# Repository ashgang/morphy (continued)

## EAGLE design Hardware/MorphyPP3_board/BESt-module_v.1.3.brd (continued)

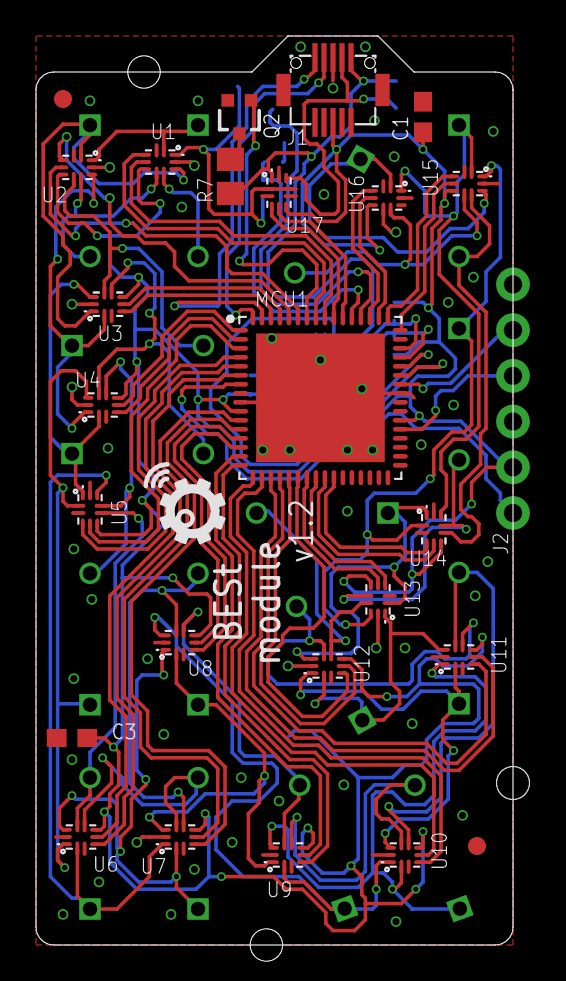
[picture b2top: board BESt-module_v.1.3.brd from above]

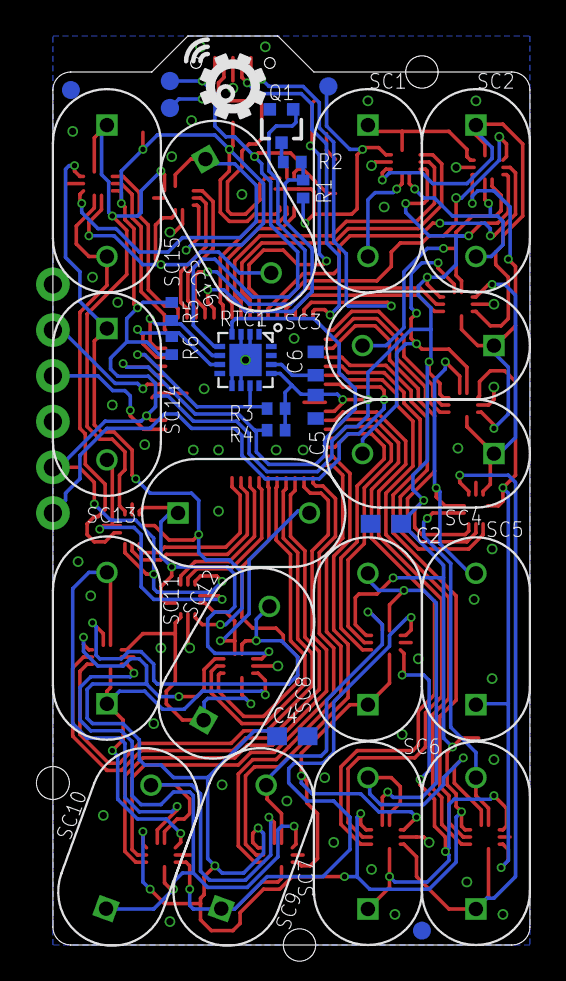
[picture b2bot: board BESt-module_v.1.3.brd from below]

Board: 2 copper layers, 26.5 x 50.5 mm, 61 parts (34 on the bottom side), 86 nets.

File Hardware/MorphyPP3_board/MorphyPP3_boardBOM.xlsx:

Comment | Description | Designator | Footprint | LibRef | Quantity
0.1uF | 0.1碌F ceramic capacitors A capacitor is a passive two-terminal electrical compo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 | C1, C2, C3, C4 | 0603 | 0.1UF-0603-25V-5% | 4
C-USC0402 | CAPACITOR, American symbol | C5, C6 | C0402 | C-USC0402 | 2
FIDUCIAL1X2 | Fiducial Alignment Points Point-of-reference for pick-and-place machines and ot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 | FD1, FD2, FD3, FD4 | FIDUCIAL-1X2 | FIDUCIAL1X2 | 4
AMPHENOL-BERGSTAK®-10POSPLUG | Amphenol鈥檚 BergStak庐 0.5mm is a comprehensive and versatile board-to-board solu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 | J1 | 10132797-10POS-PLUG | AMPHENOL-BERGSTAK®-10POSPLUG | 1
CONN_06NO_SILK_NO_POP | Multi connection point. Often used as Generic Header-pin footprint for 0.1 inch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 | J2 | 1X06_NO_SILK | CONN_06NO_SILK_NO_POP | 1
IIOT |  | LOGO1, LOGO2 | IIOT | IIOT | 2
PIC18(L)F65/66K40MR | 64-Pin, Low-Power, High-Performance Microcontrollers with XLP Technology | MCU1 | QFN50P900X900X100-65T715N | PIC18(L)F65/66K40MR | 1
310mA/60V/1.6Ω | N-channel MOSFETs Voltage controlled devices that allow control of high current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 | Q1, Q2 | SOT323 | MOSFET-NCH-2N7002PW | 2
R-EU_R0402 | RESISTOR, European symbol | R1, R2, R3, R4, R5, R6 | R0402 | R-EU_R0402 | 6
R-US_R0805 | RESISTOR, American symbol | R7 | R0805 | R-US_R0805 | 1
AB1805 |  | RTC1 | QFN-16-3X3 | AB1805 | 1
PM-5R0H/V104-R-VER | CAP 100MF -20% +80% 5V T/H | SC1, SC2, SC3, SC4, SC5, SC6, SC7, SC8, SC9, SC10, SC11, SC12, SC13, SC14, SC15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 | EATON-13X11.3X6-V | PM-5R0H/V104-R-VER | 16
TEST-POINT3X4 | SparkFun Test Points Bare copper test points for troubleshooting or In-Circuit-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 | TP1, TP2, TP3 | PAD.03X.04 | TEST-POINT3X4 | 3
ADG824 | 0.5 鈩?CMOS 1.65 V to 3.6 V Dual SPDT/2:1 Mux in Mini LFCSP Package | U1, U2, U3, U4, U5, U6, U7, U8, U9, U10, U11, U12, U13, U14, U15, U16, U17 | CP-10-10 | ADG824 | 17

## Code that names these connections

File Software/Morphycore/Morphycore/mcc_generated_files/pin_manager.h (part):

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// get/set C13_N_SW aliases
#define C13_N_SW_TRIS                 TRISAbits.TRISA1
#define C13_N_SW_LAT                  LATAbits.LATA1
#define C13_N_SW_PORT                 PORTAbits.RA1
#define C13_N_SW_WPU                  WPUAbits.WPUA1
#define C13_N_SW_OD                   ODCONAbits.ODCA1
#define C13_N_SW_ANS                  ANSELAbits.ANSELA1
#define C13_N_SW_SetHigh()            do { LATAbits.LATA1 = 1; } while(0)
#define C13_N_SW_SetLow()             do { LATAbits.LATA1 = 0; } while(0)
#define C13_N_SW_Toggle()             do { LATAbits.LATA1 = ~LATAbits.LATA1; } while(0)
#define C13_N_SW_GetValue()           PORTAbits.RA1
#define C13_N_SW_SetDigitalInput()    do { TRISAbits.TRISA1 = 1; } while(0)
#define C13_N_SW_SetDigitalOutput()   do { TRISAbits.TRISA1 = 0; } while(0)
#define C13_N_SW_SetPullup()          do { WPUAbits.WPUA1 = 1; } while(0)
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// get/set C12_N_SW aliases
#define C12_N_SW_TRIS                 TRISAbits.TRISA3
#define C12_N_SW_LAT                  LATAbits.LATA3
#define C12_N_SW_PORT                 PORTAbits.RA3
#define C12_N_SW_WPU                  WPUAbits.WPUA3
#define C12_N_SW_OD                   ODCONAbits.ODCA3
#define C12_N_SW_ANS                  ANSELAbits.ANSELA3
#define C12_N_SW_SetHigh()            do { LATAbits.LATA3 = 1; } while(0)
#define C12_N_SW_SetLow()             do { LATAbits.LATA3 = 0; } while(0)
#define C12_N_SW_Toggle()             do { LATAbits.LATA3 = ~LATAbits.LATA3; } while(0)
#define C12_N_SW_GetValue()           PORTAbits.RA3
#define C12_N_SW_SetDigitalInput()    do { TRISAbits.TRISA3 = 1; } while(0)
#define C12_N_SW_SetDigitalOutput()   do { TRISAbits.TRISA3 = 0; } while(0)
#define C12_N_SW_SetPullup()          do { WPUAbits.WPUA3 = 1; } while(0)
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// get/set C15_N_SW aliases
#define C15_N_SW_TRIS                 TRISBbits.TRISB0
#define C15_N_SW_LAT                  LATBbits.LATB0
#define C15_N_SW_PORT                 PORTBbits.RB0
#define C15_N_SW_WPU                  WPUBbits.WPUB0
#define C15_N_SW_OD                   ODCONBbits.ODCB0
#define C15_N_SW_ANS                  ANSELBbits.ANSELB0
#define C15_N_SW_SetHigh()            do { LATBbits.LATB0 = 1; } while(0)
#define C15_N_SW_SetLow()             do { LATBbits.LATB0 = 0; } while(0)
#define C15_N_SW_Toggle()             do { LATBbits.LATB0 = ~LATBbits.LATB0; } while(0)
#define C15_N_SW_GetValue()           PORTBbits.RB0
#define C15_N_SW_SetDigitalInput()    do { TRISBbits.TRISB0 = 1; } while(0)
#define C15_N_SW_SetDigitalOutput()   do { TRISBbits.TRISB0 = 0; } while(0)
#define C15_N_SW_SetPullup()          do { WPUBbits.WPUB0 = 1; } while(0)
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// get/set LowVoltagePin aliases
#define LowVoltagePin_TRIS                 TRISBbits.TRISB7
#define LowVoltagePin_LAT                  LATBbits.LATB7
#define LowVoltagePin_PORT                 PORTBbits.RB7
#define LowVoltagePin_WPU                  WPUBbits.WPUB7
#define LowVoltagePin_OD                   ODCONBbits.ODCB7
#define LowVoltagePin_ANS                  ANSELBbits.ANSELB7
#define LowVoltagePin_SetHigh()            do { LATBbits.LATB7 = 1; } while(0)
#define LowVoltagePin_SetLow()             do { LATBbits.LATB7 = 0; } while(0)
#define LowVoltagePin_Toggle()             do { LATBbits.LATB7 = ~LATBbits.LATB7; } while(0)
#define LowVoltagePin_GetValue()           PORTBbits.RB7
#define LowVoltagePin_SetDigitalInput()    do { TRISBbits.TRISB7 = 1; } while(0)
#define LowVoltagePin_SetDigitalOutput()   do { TRISBbits.TRISB7 = 0; } while(0)
#define LowVoltagePin_SetPullup()          do { WPUBbits.WPUB7 = 1; } while(0)
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// get/set VSYS_SW aliases
#define VSYS_SW_TRIS                 TRISDbits.TRISD1
#define VSYS_SW_LAT                  LATDbits.LATD1
#define VSYS_SW_PORT                 PORTDbits.RD1
#define VSYS_SW_WPU                  WPUDbits.WPUD1
#define VSYS_SW_OD                   ODCONDbits.ODCD1
#define VSYS_SW_ANS                  ANSELDbits.ANSELD1
#define VSYS_SW_SetHigh()            do { LATDbits.LATD1 = 1; } while(0)
#define VSYS_SW_SetLow()             do { LATDbits.LATD1 = 0; } while(0)
#define VSYS_SW_Toggle()             do { LATDbits.LATD1 = ~LATDbits.LATD1; } while(0)
#define VSYS_SW_GetValue()           PORTDbits.RD1
#define VSYS_SW_SetDigitalInput()    do { TRISDbits.TRISD1 = 1; } while(0)
#define VSYS_SW_SetDigitalOutput()   do { TRISDbits.TRISD1 = 0; } while(0)
#define VSYS_SW_SetPullup()          do { WPUDbits.WPUD1 = 1; } while(0)
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// get/set VEH_SW aliases
#define VEH_SW_TRIS                 TRISDbits.TRISD2
#define VEH_SW_LAT                  LATDbits.LATD2
#define VEH_SW_PORT                 PORTDbits.RD2
#define VEH_SW_WPU                  WPUDbits.WPUD2
#define VEH_SW_OD                   ODCONDbits.ODCD2
#define VEH_SW_ANS                  ANSELDbits.ANSELD2
#define VEH_SW_SetHigh()            do { LATDbits.LATD2 = 1; } while(0)
#define VEH_SW_SetLow()             do { LATDbits.LATD2 = 0; } while(0)
#define VEH_SW_Toggle()             do { LATDbits.LATD2 = ~LATDbits.LATD2; } while(0)
#define VEH_SW_GetValue()           PORTDbits.RD2
#define VEH_SW_SetDigitalInput()    do { TRISDbits.TRISD2 = 1; } while(0)
#define VEH_SW_SetDigitalOutput()   do { TRISDbits.TRISD2 = 0; } while(0)
#define VEH_SW_SetPullup()          do { WPUDbits.WPUD2 = 1; } while(0)
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// get/set channel_AND3 aliases
#define channel_AND3_TRIS                 TRISDbits.TRISD3
#define channel_AND3_LAT                  LATDbits.LATD3
#define channel_AND3_PORT                 PORTDbits.RD3
#define channel_AND3_WPU                  WPUDbits.WPUD3
#define channel_AND3_OD                   ODCONDbits.ODCD3
#define channel_AND3_ANS                  ANSELDbits.ANSELD3
#define channel_AND3_SetHigh()            do { LATDbits.LATD3 = 1; } while(0)
#define channel_AND3_SetLow()             do { LATDbits.LATD3 = 0; } while(0)
#define channel_AND3_Toggle()             do { LATDbits.LATD3 = ~LATDbits.LATD3; } while(0)
#define channel_AND3_GetValue()           PORTDbits.RD3
#define channel_AND3_SetDigitalInput()    do { TRISDbits.TRISD3 = 1; } while(0)
#define channel_AND3_SetDigitalOutput()   do { TRISDbits.TRISD3 = 0; } while(0)
#define channel_AND3_SetPullup()          do { WPUDbits.WPUD3 = 1; } while(0)
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// get/set C16_N_SW aliases
#define C16_N_SW_TRIS                 TRISDbits.TRISD6
#define C16_N_SW_LAT                  LATDbits.LATD6
#define C16_N_SW_PORT                 PORTDbits.RD6
#define C16_N_SW_WPU                  WPUDbits.WPUD6
#define C16_N_SW_OD                   ODCONDbits.ODCD6
#define C16_N_SW_ANS                  ANSELDbits.ANSELD6
#define C16_N_SW_SetHigh()            do { LATDbits.LATD6 = 1; } while(0)
#define C16_N_SW_SetLow()             do { LATDbits.LATD6 = 0; } while(0)
#define C16_N_SW_Toggle()             do { LATDbits.LATD6 = ~LATDbits.LATD6; } while(0)
#define C16_N_SW_GetValue()           PORTDbits.RD6
#define C16_N_SW_SetDigitalInput()    do { TRISDbits.TRISD6 = 1; } while(0)
#define C16_N_SW_SetDigitalOutput()   do { TRISDbits.TRISD6 = 0; } while(0)
#define C16_N_SW_SetPullup()          do { WPUDbits.WPUD6 = 1; } while(0)
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// get/set C4_P_SW aliases
#define C4_P_SW_TRIS                 TRISEbits.TRISE0
#define C4_P_SW_LAT                  LATEbits.LATE0
#define C4_P_SW_PORT                 PORTEbits.RE0
#define C4_P_SW_WPU                  WPUEbits.WPUE0
#define C4_P_SW_OD                   ODCONEbits.ODCE0
#define C4_P_SW_ANS                  ANSELEbits.ANSELE0
#define C4_P_SW_SetHigh()            do { LATEbits.LATE0 = 1; } while(0)
#define C4_P_SW_SetLow()             do { LATEbits.LATE0 = 0; } while(0)
#define C4_P_SW_Toggle()             do { LATEbits.LATE0 = ~LATEbits.LATE0; } while(0)
#define C4_P_SW_GetValue()           PORTEbits.RE0
#define C4_P_SW_SetDigitalInput()    do { TRISEbits.TRISE0 = 1; } while(0)
#define C4_P_SW_SetDigitalOutput()   do { TRISEbits.TRISE0 = 0; } while(0)
#define C4_P_SW_SetPullup()          do { WPUEbits.WPUE0 = 1; } while(0)
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// get/set C4_N_SW aliases
#define C4_N_SW_TRIS                 TRISEbits.TRISE1
#define C4_N_SW_LAT                  LATEbits.LATE1
#define C4_N_SW_PORT                 PORTEbits.RE1
#define C4_N_SW_WPU                  WPUEbits.WPUE1
#define C4_N_SW_OD                   ODCONEbits.ODCE1
#define C4_N_SW_ANS                  ANSELEbits.ANSELE1
#define C4_N_SW_SetHigh()            do { LATEbits.LATE1 = 1; } while(0)
#define C4_N_SW_SetLow()             do { LATEbits.LATE1 = 0; } while(0)
#define C4_N_SW_Toggle()             do { LATEbits.LATE1 = ~LATEbits.LATE1; } while(0)
#define C4_N_SW_GetValue()           PORTEbits.RE1
#define C4_N_SW_SetDigitalInput()    do { TRISEbits.TRISE1 = 1; } while(0)
#define C4_N_SW_SetDigitalOutput()   do { TRISEbits.TRISE1 = 0; } while(0)
#define C4_N_SW_SetPullup()          do { WPUEbits.WPUE1 = 1; } while(0)
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#define RE2_SetHigh()            do { LATEbits.LATE2 = 1; } while(0)
#define RE2_SetLow()             do { LATEbits.LATE2 = 0; } while(0)
#define RE2_Toggle()             do { LATEbits.LATE2 = ~LATEbits.LATE2; } while(0)
#define RE2_GetValue()              PORTEbits.RE2
#define RE2_SetDigitalInput()    do { TRISEbits.TRISE2 = 1; } while(0)
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
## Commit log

2021-10-04 Repo creation
2021-10-04 folders commit
2021-10-06 additional APIs support
2021-10-06 Add schematics
2021-10-06 Folder structure changes
2021-10-06 readme changes
2021-10-06 Rename README to README.md
2021-10-07 License and documentation
2021-10-07 License for design files
2021-10-07 Adding the morphy core and readme files
2021-10-07 readme files update
